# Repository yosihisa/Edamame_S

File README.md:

# えだまめS  
えだまめSはSOMESATが開発したCanSat入門キットです。  
## 特徴  
実装済みの基板とArduino用のライブラリを用いることにより、簡単にCanSatを作ることができます。  
簡単なプログラムから順番に学んでいくことにより、CanSatの基礎を理解しながら一般的な誘導までできるようになります。  
<br>
基板はバス基板と拡張基板に分かれています。

- バス基板に載っているもの  
  - Arduinoとなるマイコン  
  - GPSモジュール  
  - 地磁気センサ  
  - SDカード  
  - 電源  

- 拡張基板に載っているもの  
  - モータードライバ  
  - モーター  
  - ニクロム線  
  - 電池  

## バス基板の拡張ポート  
この拡張ポートはGPIO,PWM,I2C,UARTなどの機能を割り当てることができます。 
オリジナルCanSatの制御ボードや、他のロボットの制御ボードとして用いることができます。

## 電源について
バス基板の入力電圧は1.7～5.5Vです。  
**絶対に5.5V以上の電圧をかけないようにしてください。**  
Vinと3.3V,GNDをショートさせないように気をつけてください。  
<br>
拡張基板に使用できる電池は**10440型リチウムイオン電池**です。　　

## Arduino IDEへのインストール方法　　
インストールが必要なライブラリは2つあります。
### MightyCore  
このボードをインストールすることにより、えだまめSに搭載されているATmega1284PをArduino IDEからプログラミングできるようになります。  
https://github.com/MCUdude/MightyCore  
### えだまめS ライブラリ
このライブラリをインストールすることにより、えだまめSの各機能を簡単な関数で使うことができるようになります。  
まず、リンク先から最新版のzipをダウンロードします。  
次にArduino IDEの　　

 >  スケッチ>ライブラリをインクルード>.ZIP形式のライブラリをインストール  
 
 を開き、ダウンロードしたZIPファイルを選択します。  
 ダウンロード先 → https://github.com/yosihisa/Edamame_S/releases  

 # 注意事項  
 えだまめSプロジェクトはまだ未完成です。  
 利用は自己責任でお願いします。  
 <br>
 各種解説ページは準備中です。  
 
 連絡先 [@n_yosihisa](https://twitter.com/n_yosihisa)

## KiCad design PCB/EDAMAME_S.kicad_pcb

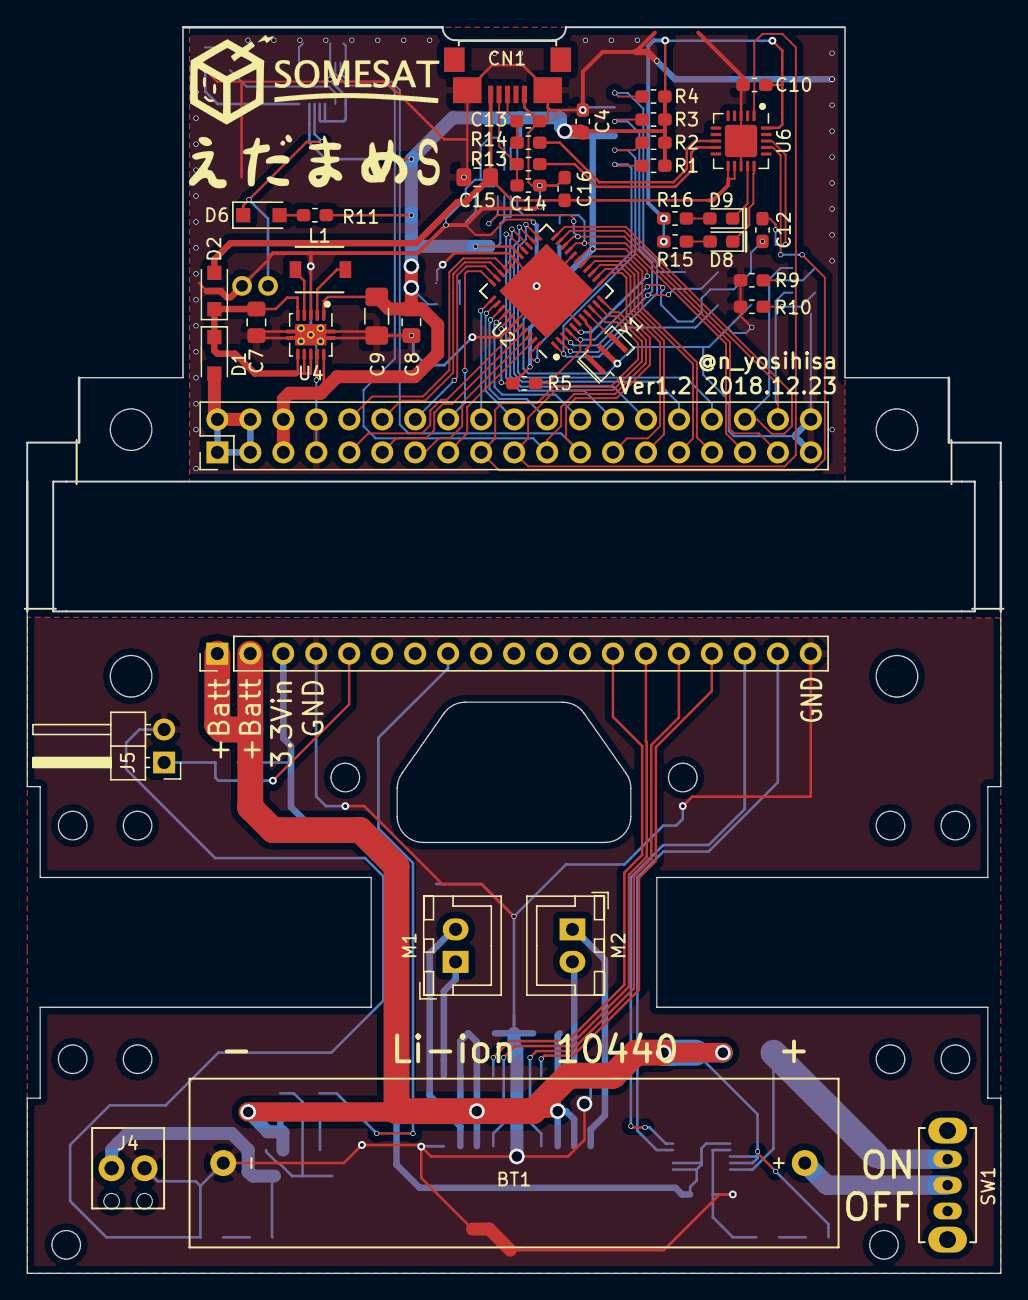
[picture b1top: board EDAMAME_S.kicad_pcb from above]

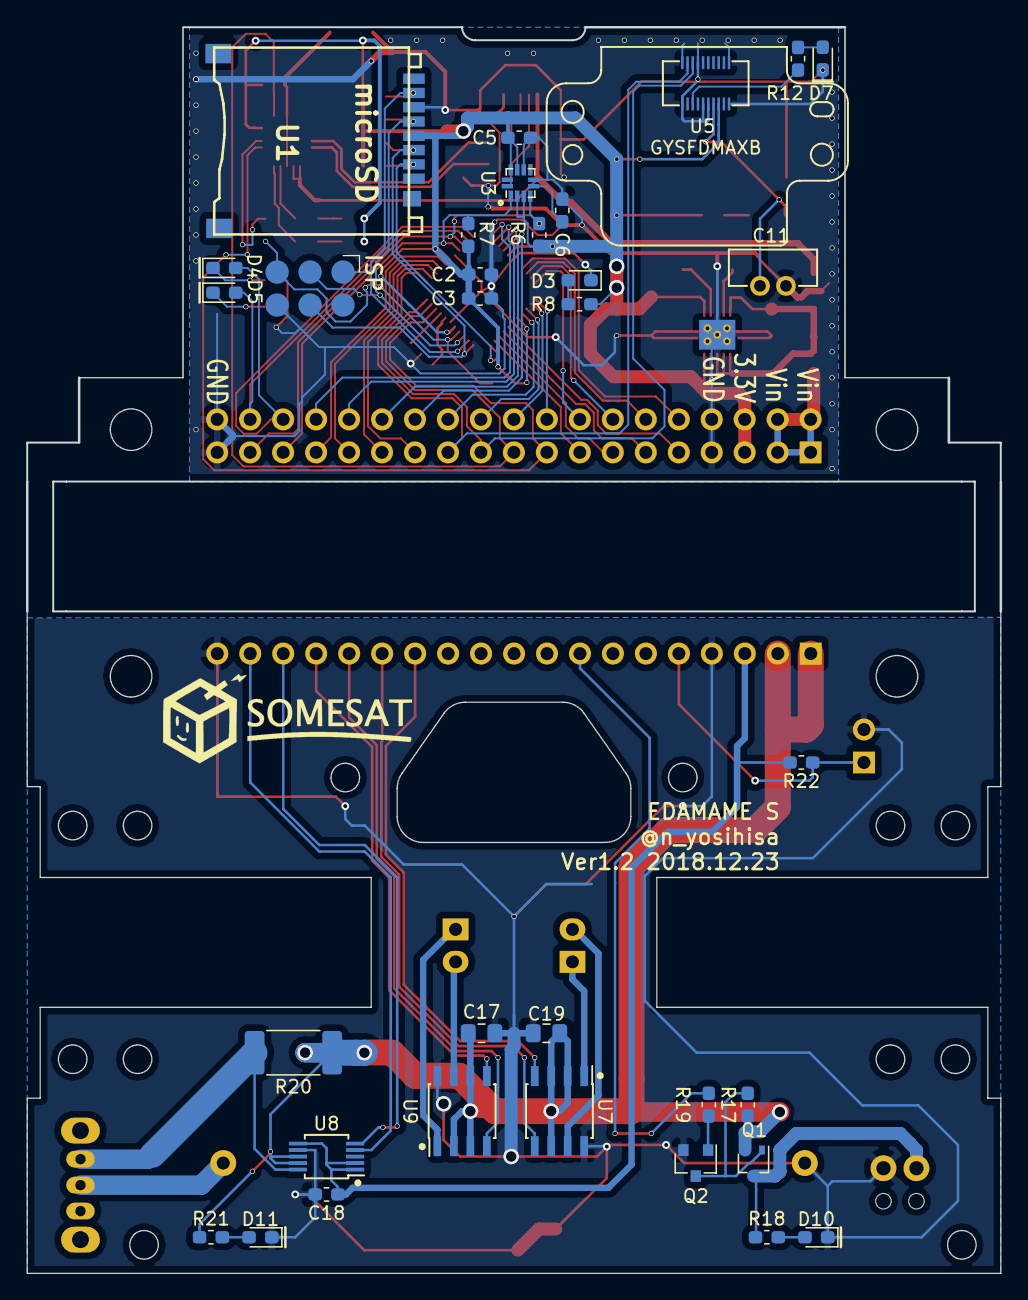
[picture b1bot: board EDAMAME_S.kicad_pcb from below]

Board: 2 copper layers, 75.0 x 96.0 mm, 74 parts (32 on the bottom side), 81 nets.

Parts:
BT1: 10440; BH-411
C2, C3, C4, C5, C6, C10, C12, C16, C18: 0.1u; C_0603_1608Metric_Pad1.05x0.95mm_HandSolder
C7, C8, C15, C17, C19: 10u; C_0805_2012Metric_Pad1.15x1.40mm_HandSolder
C9: 100u; C_1206_3216Metric_Pad1.42x1.75mm_HandSolder
C11: 0.22F 3.3V; MS621FE_FL11E
C13, C14: 47p; C_0603_1608Metric_Pad1.05x0.95mm_HandSolder
CN1: USB-B-MICRO; Micro-USB
D1, D2, D6: GS1010FL; D_SOD-123F
D3, D11: POWER; LED_0603_1608Metric_Pad1.05x0.95mm_HandSolder
D4: LED1; LED_0603_1608Metric_Pad1.05x0.95mm_HandSolder
D5: LED2; LED_0603_1608Metric_Pad1.05x0.95mm_HandSolder
D7: 1PPS; LED_0603_1608Metric_Pad1.05x0.95mm_HandSolder
D8: TX_LED; LED_0603_1608Metric_Pad1.05x0.95mm_HandSolder
D9: RX_LED; LED_0603_1608Metric_Pad1.05x0.95mm_HandSolder
D10: Nichrome; LED_0603_1608Metric_Pad1.05x0.95mm_HandSolder
J1: Conn; PinHeader_2x19_P2.54mm_Vertical
J2: ISP; AVR_ISP
J3: Conn; PinHeader_1x19_P2.54mm_Vertical
J4: Nichrome; MPT0.5_2-2.54
J5: FlightPin; PinHeader_1x02_P2.54mm_Horizontal
L1: 2.2uH; inductor_VLF4012-2R2
M1: Motor_L; JST_XH_B02B-XH-A_1x02_P2.50mm_Vertical
M2: Motor_R; JST_XH_B02B-XH-A_1x02_P2.50mm_Vertical
Q1: MTM231102LBF; SOT-323_SC-70
Q2: 2SC2712; SOT-23
R1, R2, R3, R4, R5: 10k; R_0603_1608Metric_Pad1.05x0.95mm_HandSolder
R6, R7: 2.2k; R_0603_1608Metric_Pad1.05x0.95mm_HandSolder
R8, R9, R10, R12, R15, R16: 1k; R_0603_1608Metric_Pad1.05x0.95mm_HandSolder
R11: 100; R_0603_1608Metric_Pad1.05x0.95mm_HandSolder
R13, R14: 33; R_0603_1608Metric_Pad1.05x0.95mm_HandSolder
R17, R19, R22: 10K; R_0603_1608Metric_Pad1.05x0.95mm_HandSolder
R18, R21: 1K; R_0603_1608Metric_Pad1.05x0.95mm_HandSolder
R20: 10m; R_2512_6332Metric_Pad1.52x3.35mm_HandSolder
SW1: power; SS-12D01-VG4
U1: microSD
U2: ATMEGA1284P-MU; QFN-44-1EP_7x7mm_P0.5mm_EP5.15x5.15mm
U3: LSM303C; LGA-12_2x2mm_P0.5mm_HandSolder
U4: TPS63001; Texas_S-PVSON-N10_ThermalVias
U5: GYSFDMAXB
U6: FT231XQ; QFN-20-1EP_4x4mm_P0.5mm_EP2.5x2.5mm
U7, U9: BD6211F; SOIC-8_3.9x4.9mm_P1.27mm
U8: INA226; MSOP-10_3x3mm_P0.5mm
Y1: 12MHz; Resonator_SMD_muRata_CSTxExxV-3Pin_3.0x1.1mm

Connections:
+3V3: C2.1, C3.1, C4.1, C5.1, C8.1, C9.1, C10.1, J1.5, J1.6, R1.2, R2.2, R3.2, R4.2, R5.1, R6.1, R7.1, R8.2, R11.1, R15.1, R16.1, U1.4, U2.5, U2.17, U2.27, U2.38, U3.2, U3.3, U3.9, U3.10, U4.1, U4.10, U5.16, U6.20
+5V: C15.1, C16.1, CN1.1, D2.2, U6.11, U6.12
+BATT: C17.1, C19.1, J3.1, J3.2, Q1.2, R17.2, R20.1, R21.1, U7.2, U7.3, U7.6, U8.8, U8.9, U9.2, U9.3, U9.6
/EDAMAME_S_Ex/FlightPin: J3.5, J5.1, R22.1
/EDAMAME_S_Ex/MOTOR_LF: J3.13, U7.4
/EDAMAME_S_Ex/MOTOR_LR: J3.14, U7.5
/EDAMAME_S_Ex/MOTOR_RF: J3.16, U9.5
/EDAMAME_S_Ex/MOTOR_RR: J3.15, U9.4
/EDAMAME_S_Ex/Nichrome: J3.8, R19.2
/EDAMAME_S_Ex/SCL: J3.17, U8.5
/EDAMAME_S_Ex/SDA: J3.18, U8.4
/EDAMAME_S_core/0: J1.9, U2.40
/EDAMAME_S_core/1: J1.11, U2.41
/EDAMAME_S_core/2: J1.13, U2.42
/EDAMAME_S_core/3-: J1.15, U2.43
/EDAMAME_S_core/12-: J1.25, U2.13
/EDAMAME_S_core/13-: J1.27, U2.14
/EDAMAME_S_core/14-: J1.29, U2.15
/EDAMAME_S_core/15-: J1.31, U2.16
/EDAMAME_S_core/18: D5.2, J1.36, U2.21
/EDAMAME_S_core/19: D4.2, J1.34, U2.22
/EDAMAME_S_core/20: J1.32, U2.23
/EDAMAME_S_core/21: J1.30, U2.24
/EDAMAME_S_core/22: J1.28, U2.25
/EDAMAME_S_core/23: J1.26, U2.26
/EDAMAME_S_core/A0: J1.24, U2.37
/EDAMAME_S_core/A1: J1.22, U2.36
/EDAMAME_S_core/A2: J1.20, U2.35
/EDAMAME_S_core/A3: J1.18, U2.34
/EDAMAME_S_core/A4: J1.16, U2.33
/EDAMAME_S_core/A5: J1.14, U2.32
/EDAMAME_S_core/A6: J1.12, U2.31
/EDAMAME_S_core/A7: J1.10, U2.30
/EDAMAME_S_core/AVR→GPS: J1.23, U2.12, U5.3
/EDAMAME_S_core/AVR→PC: J1.19, U2.10, U6.1
/EDAMAME_S_core/GPS→AVR: J1.21, U2.11, U5.5
/EDAMAME_S_core/I2C_SCL: J1.33, R7.2, U2.19, U3.1
/EDAMAME_S_core/I2C_SDA: J1.35, R6.2, U2.20, U3.4
/EDAMAME_S_core/MISO: J2.1, R4.1, U1.7, U2.2
/EDAMAME_S_core/MOSI: J2.4, R2.1, U1.3, U2.1
/EDAMAME_S_core/PC→AVR: J1.17, U2.9, U6.17
/EDAMAME_S_core/RST: C12.2, J2.5, R5.2, U2.4
/EDAMAME_S_core/SCK: J2.3, R3.1, U1.5, U2.3
/EDAMAME_S_core/SS: R1.1, U1.2, U2.44
GND: C2.2, C3.2, C4.2, C5.2, C6.2, C7.2, C8.2, C9.2, C10.2, C11.2, C13.2, C14.2, C15.2, C16.2, CN1.5, CN1.6, CN1.7, D3.1, D7.1, J1.7, J1.8, J1.37, J1.38, J2.6, R9.2, R10.2, U1.6, U2.6, U2.18, U2.28, U2.39, U3.6, U3.8, U4.3, U4.9, U4.11, U5.1, U5.2, U5.7, U5.10, U5.12, U5.19, U5.20, U6.3, U6.13, U6.21, Y1.2
GNDPWR: BT1.2, C17.2, C18.2, C19.2, D10.1, D11.1, J3.4, J3.19, J4.2, J5.2, Q2.2, U7.8, U8.7, U9.8
unnamed: BT1.1, SW1.2
unnamed: C6.1, U3.5
unnamed: C7.1, D1.1, D2.1, U4.5, U4.6, U4.7, U4.8
unnamed: C11.1, D6.1, U5.14
unnamed: C12.1, U6.18
unnamed: C13.1, CN1.3, R14.2
unnamed: C14.1, CN1.2, R13.2
unnamed: D1.2, J1.1, J1.2, J1.3, J1.4
unnamed: D3.2, R8.1
unnamed: D4.1, R9.1
unnamed: D5.1, R10.1
unnamed: D6.2, R11.2
unnamed: D7.2, R12.1
unnamed: D8.1, U6.15
unnamed: D8.2, R15.2
unnamed: D9.1, U6.14
unnamed: D9.2, R16.2
unnamed: D10.2, R18.2
unnamed: D11.2, R21.2
unnamed: J4.1, Q1.3, R18.1
unnamed: L1.1, U4.4
unnamed: L1.2, U4.2
unnamed: M1.1, U7.1
unnamed: M1.2, U7.7
unnamed: M2.1, U9.1
unnamed: M2.2, U9.7
unnamed: Q1.1, Q2.3, R17.1
unnamed: Q2.1, R19.1
unnamed: R12.2, U5.6
unnamed: R13.1, U6.9
unnamed: R14.1, U6.8
unnamed: R20.2, SW1.1, U8.10
unnamed: U2.7, Y1.1
unnamed: U2.8, Y1.3
VCC: C18.1, J3.3, R22.2, U8.1, U8.2, U8.6

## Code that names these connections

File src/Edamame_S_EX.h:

#ifndef _Edamame_S_EX_h
#define _Edamame_S_EX_h

#include <Arduino.h>
#include <Wire.h>


#define INA226_ADDR 0x45
#define MOTOR_RF  13
#define MOTOR_RR  12
#define MOTOR_LF  14
#define MOTOR_LR  15
#define NICHROME  3
#define FLIGHT_PIN 0

void set_pinMode();

void motor(int ,int);
void nichrome(int);

void ina226_init();
long ina226_voltage();
long ina226_current();

#endif

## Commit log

2019-02-15 Ver0.1.0
    Add library
    Ad ex01-03,05 (LED,UART,PWM,I2C)
2019-02-19 Add SD,GPS
2019-02-19 Update GPS
2019-02-20 Add Calibration
2019-02-20 Add nichrome,arg_calc
2019-02-21 Fixed Sign of longitude
2019-02-22 Add STL
2019-02-22 Update librares
2019-02-22 Fixed Motor rotation direction
2019-03-04 Add PCB (0.2mmビアあり)
2019-03-07 Fix set_gpsHispeed
